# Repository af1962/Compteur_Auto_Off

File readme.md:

Le montage qui est présenté içi est un compteur de passage de pièces. Il s'agit de la seconde version (la 1er était à base d'un atmega328).
Réalisé avec Kicad pour la partie soft et à l'aide d'une CNC pour la gravure à l'anglaise du PCB.
La version finale mise en production comporte une fonction d'auto extinction automatique.
L'automaintien est confié à un relais qui coupe l'alimention après le temps prédéfini.
Il existe aussi une version avec mémorisation du dernier comptage. Le problème étant lié à la durée de vie de la mémoire EEPROM. Dans les conditions de production actuelle (environ 250 pièces par jour) la durée de vie est d'environ 400 jours.
Il faudrait un algorithme qui modifie l'emplacement mémoire de la sauvegarde, après un certain nombre de comptage.

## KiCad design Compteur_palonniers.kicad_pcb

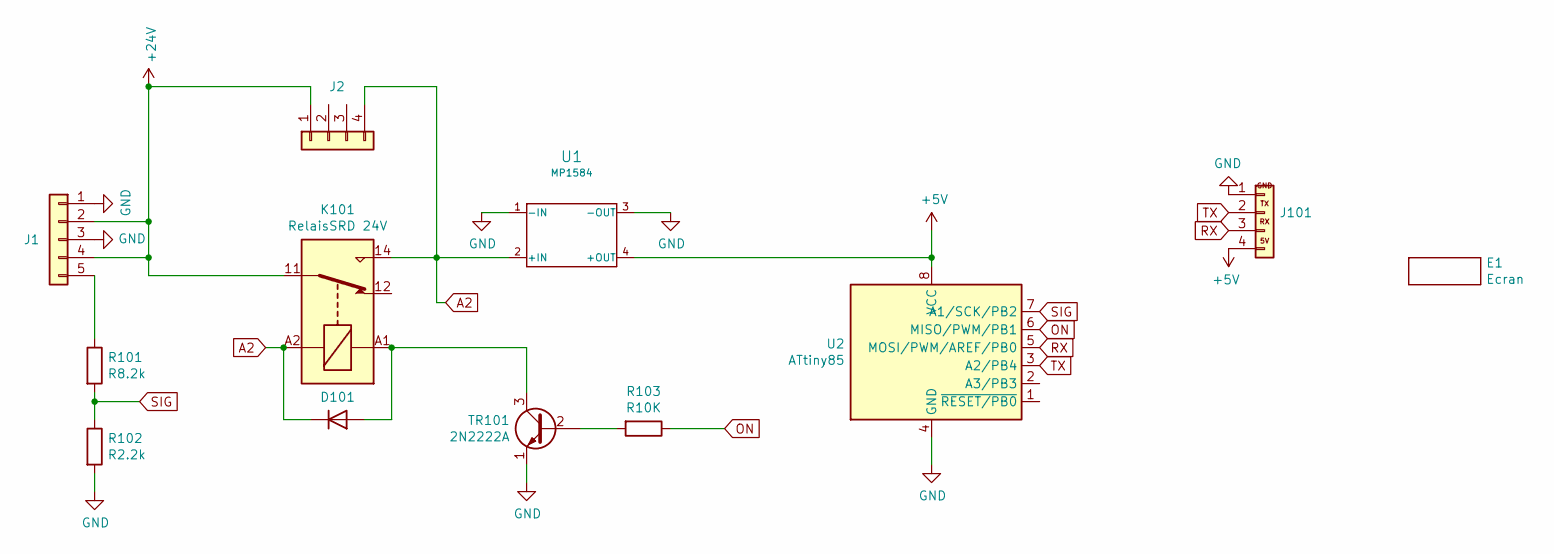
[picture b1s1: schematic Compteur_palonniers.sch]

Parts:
D101: Diode_1N4148; diode_do35
E1: Ecran; Nextion_24
J1: Conn_01x05; TerminalBlock_Phoenix_MKDS-1,5-5-5.08_1x05_P5.08mm_Horizont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
J2: Conn_01x04; pin_strip_4
J101: Connecteur_Nextion; JST_XH_B04B-XH-A_04x2.50mm_Straight
K101: RelaisSRD 24V; Relais_SRD
R101: R8.2k; R_025W
R102: R2.2k; R_025W
R103: R10K; R_025W
TR101: 2N2222A; TO-92
U1: MP1584
U2: ATtiny85; dil_8-300_socket

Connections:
14: D101.1 (K), J2.4, K101.14, K101.A2, U1.2 (+IN)
+5V: J101.4, U1.4 (+OUT), U2.8 (VCC)
+24V: J1.2, J1.4, J2.1, K101.11
GND: J1.1, J1.3, J101.1, R102.2, TR101.1 (E), U1.1 (-IN), U1.3 (-OUT), U2.4 (GND)
unnamed: D101.2 (A), K101.A1, TR101.3 (C)
unnamed: J1.5, R101.1
unnamed: R103.2, TR101.2 (B)
ON: R103.1, U2.6 (MISO/PWM/PB1)
RX: J101.3, U2.5 (MOSI/PWM/AREF/PB0)
SIG: R101.2, R102.1, U2.7 (A1/SCK/PB2)
TX: J101.2, U2.3 (A2/PB4)

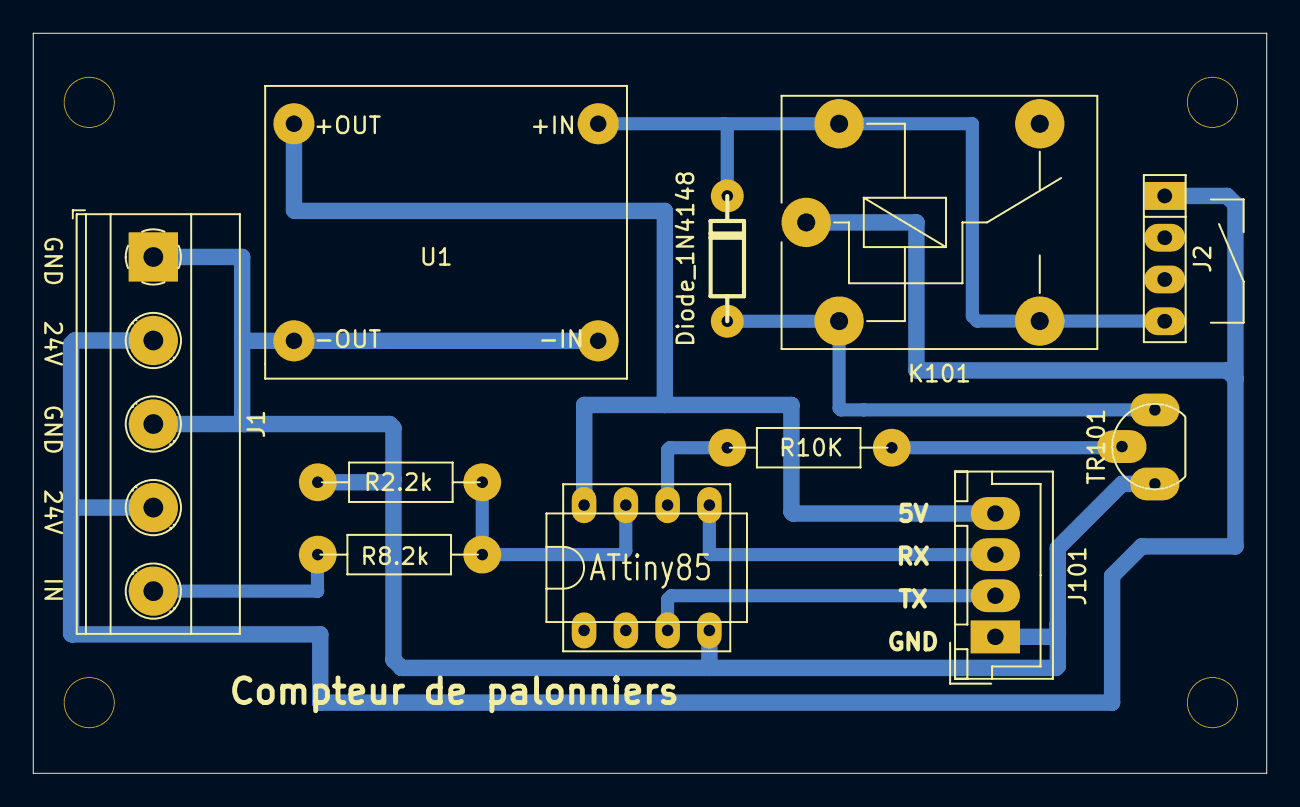
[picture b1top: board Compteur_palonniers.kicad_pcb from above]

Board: 2 copper layers, 75.0 x 45.0 mm, 12 parts (1 on the bottom side), 11 nets.

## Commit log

2023-05-07 Init
2023-05-07 Version finale
2023-05-08 Version fianale
2023-05-08 Photos
2023-05-09 EEPROM progarmme
2023-05-16 Modification sauvegarde dernier comptage
2023-05-16 Readme
2023-05-16 Correction des bugs
2023-05-16 Afficheur sans Off
2023-05-17 commentaires
2023-05-17 Modif alim
2023-05-17 Correction tracé pcb
